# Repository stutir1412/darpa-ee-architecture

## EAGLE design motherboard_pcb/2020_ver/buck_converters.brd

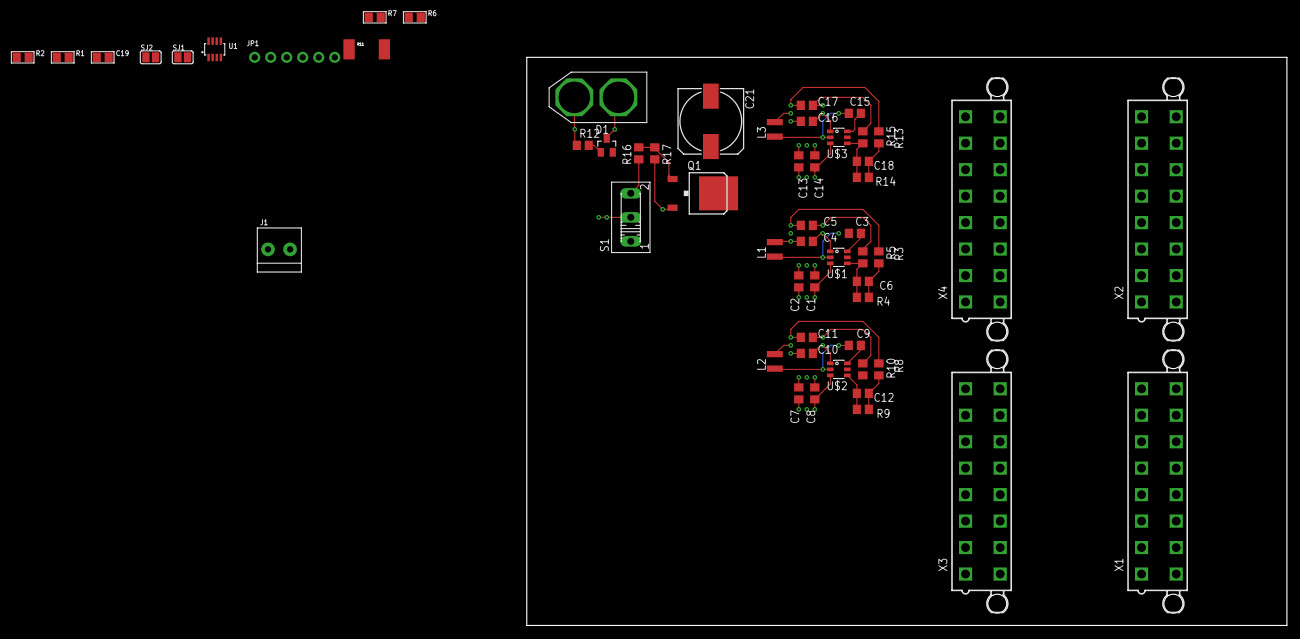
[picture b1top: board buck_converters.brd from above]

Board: 2 copper layers, 120.7 x 90.2 mm, 56 parts (0 on the bottom side), 27 nets.

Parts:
C1, C7, C13: 10uF; C0805
C2, C3, C8, C9, C14, C15: 0.1uF; C0805
C4, C5, C10, C11, C16, C17: 22uF; C0805
C6, C18: 75pF; C0805
C12: 100pF; C0805
C19: 0.1µF; 0805
C21: 153CLV-1010
D1: BAS40; SOT23
J1: TERMBLOCK_1X2-3.5MM; 1X2-3.5MM
JP1: 1X06_ROUND_70
L1, L3: 10uH; SM-NE29
L2: 15uH; SM-NE29
Q1: IRFR5305; D-PAK_TO252AA
R1, R2, R6, R7: 10K; 0805
R3, R8, R13: 49.9R; R0805
R4, R9, R14: 100K; R0805
R5: 11K; R0805
R10: 5.23K; R0805
R11: 0.01/1% (PT2512FK-070R1L); 2512
R12, R16, R17: 10K; R0805
R15: 13.3K; R0805
S1: 255SB
SJ1, SJ2: SOLDERJUMPER_REFLOW_NOPASTE
U1: SOT23-8
U$1, U$2, U$3: TPS54302; SOT23-6
U$9: XT60
X1, X2, X3, X4: 5566-16

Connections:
5V: C16.1, C17.1, L3.2, R13.2
6V: C4.1, C5.1, L1.2, R3.2
12V: C10.1, C11.1, L2.2, R8.2
GND: C1.2, C2.2, C4.2, C5.2, C7.2, C8.2, C10.2, C11.2, C13.2, C14.2, C16.2, C17.2, C19.2, C21.-, JP1.2, R1.1, R2.1, R5.1, R10.1, R12.1, R15.1, S1.2, U1.3, U$1.1, U$2.1, U$3.1, U$9.-
unnamed: C6.1, R3.1, R4.2
unnamed: C6.2, R4.1, R5.2, U$1.4
unnamed: R2.2, SJ2.2, U1.8
unnamed: C3.1, U$1.6
unnamed: C3.2, L1.1, U$1.2
unnamed: C12.1, R8.1, R9.2
unnamed: C12.2, R9.1, R10.2, U$2.4
unnamed: R1.2, SJ1.2, U1.7
unnamed: C9.1, U$2.6
unnamed: C9.2, L2.1, U$2.2
unnamed: C18.1, R13.1, R14.2
unnamed: C18.2, R14.1, R15.2, U$3.4
unnamed: C15.1, U$3.6
unnamed: C15.2, L3.1, U$3.2
unnamed: D1.1, R12.2
unnamed: R16.1, S1.3
unnamed: Q1.1, R16.2, R17.1
SCL: JP1.3, R6.1, U1.5
SDA: JP1.4, R7.1, U1.6
VCC: C19.1, D1.3, JP1.1, Q1.3, R6.2, R7.2, R17.2, SJ1.1, SJ2.1, U1.4, U$9.+
VIN: C1.1, C2.1, C7.1, C8.1, C13.1, C14.1, C21.+, Q1.4, U$1.3, U$2.3, U$3.3
VIN+: J1.2, JP1.6, R11.2, U1.1
VIN-: J1.1, JP1.5, R11.1, U1.2
